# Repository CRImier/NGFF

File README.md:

# [NGFF](https://github.com/sto-pi/NGFF)

### [NGFF简介](https://github.com/sto-pi/NGFF)

[NGFF](https://github.com/sto-pi/NGFF) (Next Generation Form Factor)，与 NGFF 并列的是 2.5"（2.5”硬盘（包括HDD和SSD）厚度一般为9.5mm和7mm），NGFF现在已经改名为M.2，M.2有SATA 和PCIe两种总线标准。

M.2接口是一种新的主机接口方案，可以兼容多种通信协议，如sata、PCIe、USB、HSIC、UART、SMBus等。

M.2接口是为超极本（Ultrabook）量身定做的新一代接口标准，以取代原来的mSATA接口。无论是更小巧的规格尺寸，还是更高的传输性能，M.2都远胜于mSATA。

M.2接口，是Intel推出的一种替代MSATA新的接口规范。其实，对于桌面台式机用户来讲，SATA接口已经足以满足大部分用户的需求了，不过考虑到超极本用户的存储需求，Intel才急切的推出了这种新的接口标准。所以，我们在华硕、技嘉、微星等发布的新的9系列主板上都看到了这种新的M.2接口，现已普及。 [1]
与MSATA相比，M.2主要有两个方面的优势。第一是速度方面的优势。M.2接口有两种类型：Socket 2（B key——ngff）和Socket 3（M key——nvme），其中Socket2支持SATA、PCI-E X2接口，而如果采用PCI-E ×2接口标准，最大的读取速度可以达到700MB/s，写入也能达到550MB/s。而其中的Socket 3可支持PCI-E ×4接口，理论带宽可达4GB/s。

第二个是体积方面的优势。虽然，MSATA的固态硬盘体积已经足够小了，但相比M.2接口的固态硬盘，MSATA仍然没有任何优势可言。M.2标准的SSD同mSATA一样可以进行单面NAND闪存颗粒的布置，也可以进行双面布置，其中单面布置的总厚度仅有2.75mm，而双面布置的厚度也仅为3.85mm。而mSATA在体积上的劣势就明显的多，51mm×30mm的尺寸让mSATA在面积上不占优势，而4.85mm的单面布置厚度跟M.2比起来也显得厚了太多。另外，即使在大小相同的情况下，M.2也可以提供更高的存储容量。

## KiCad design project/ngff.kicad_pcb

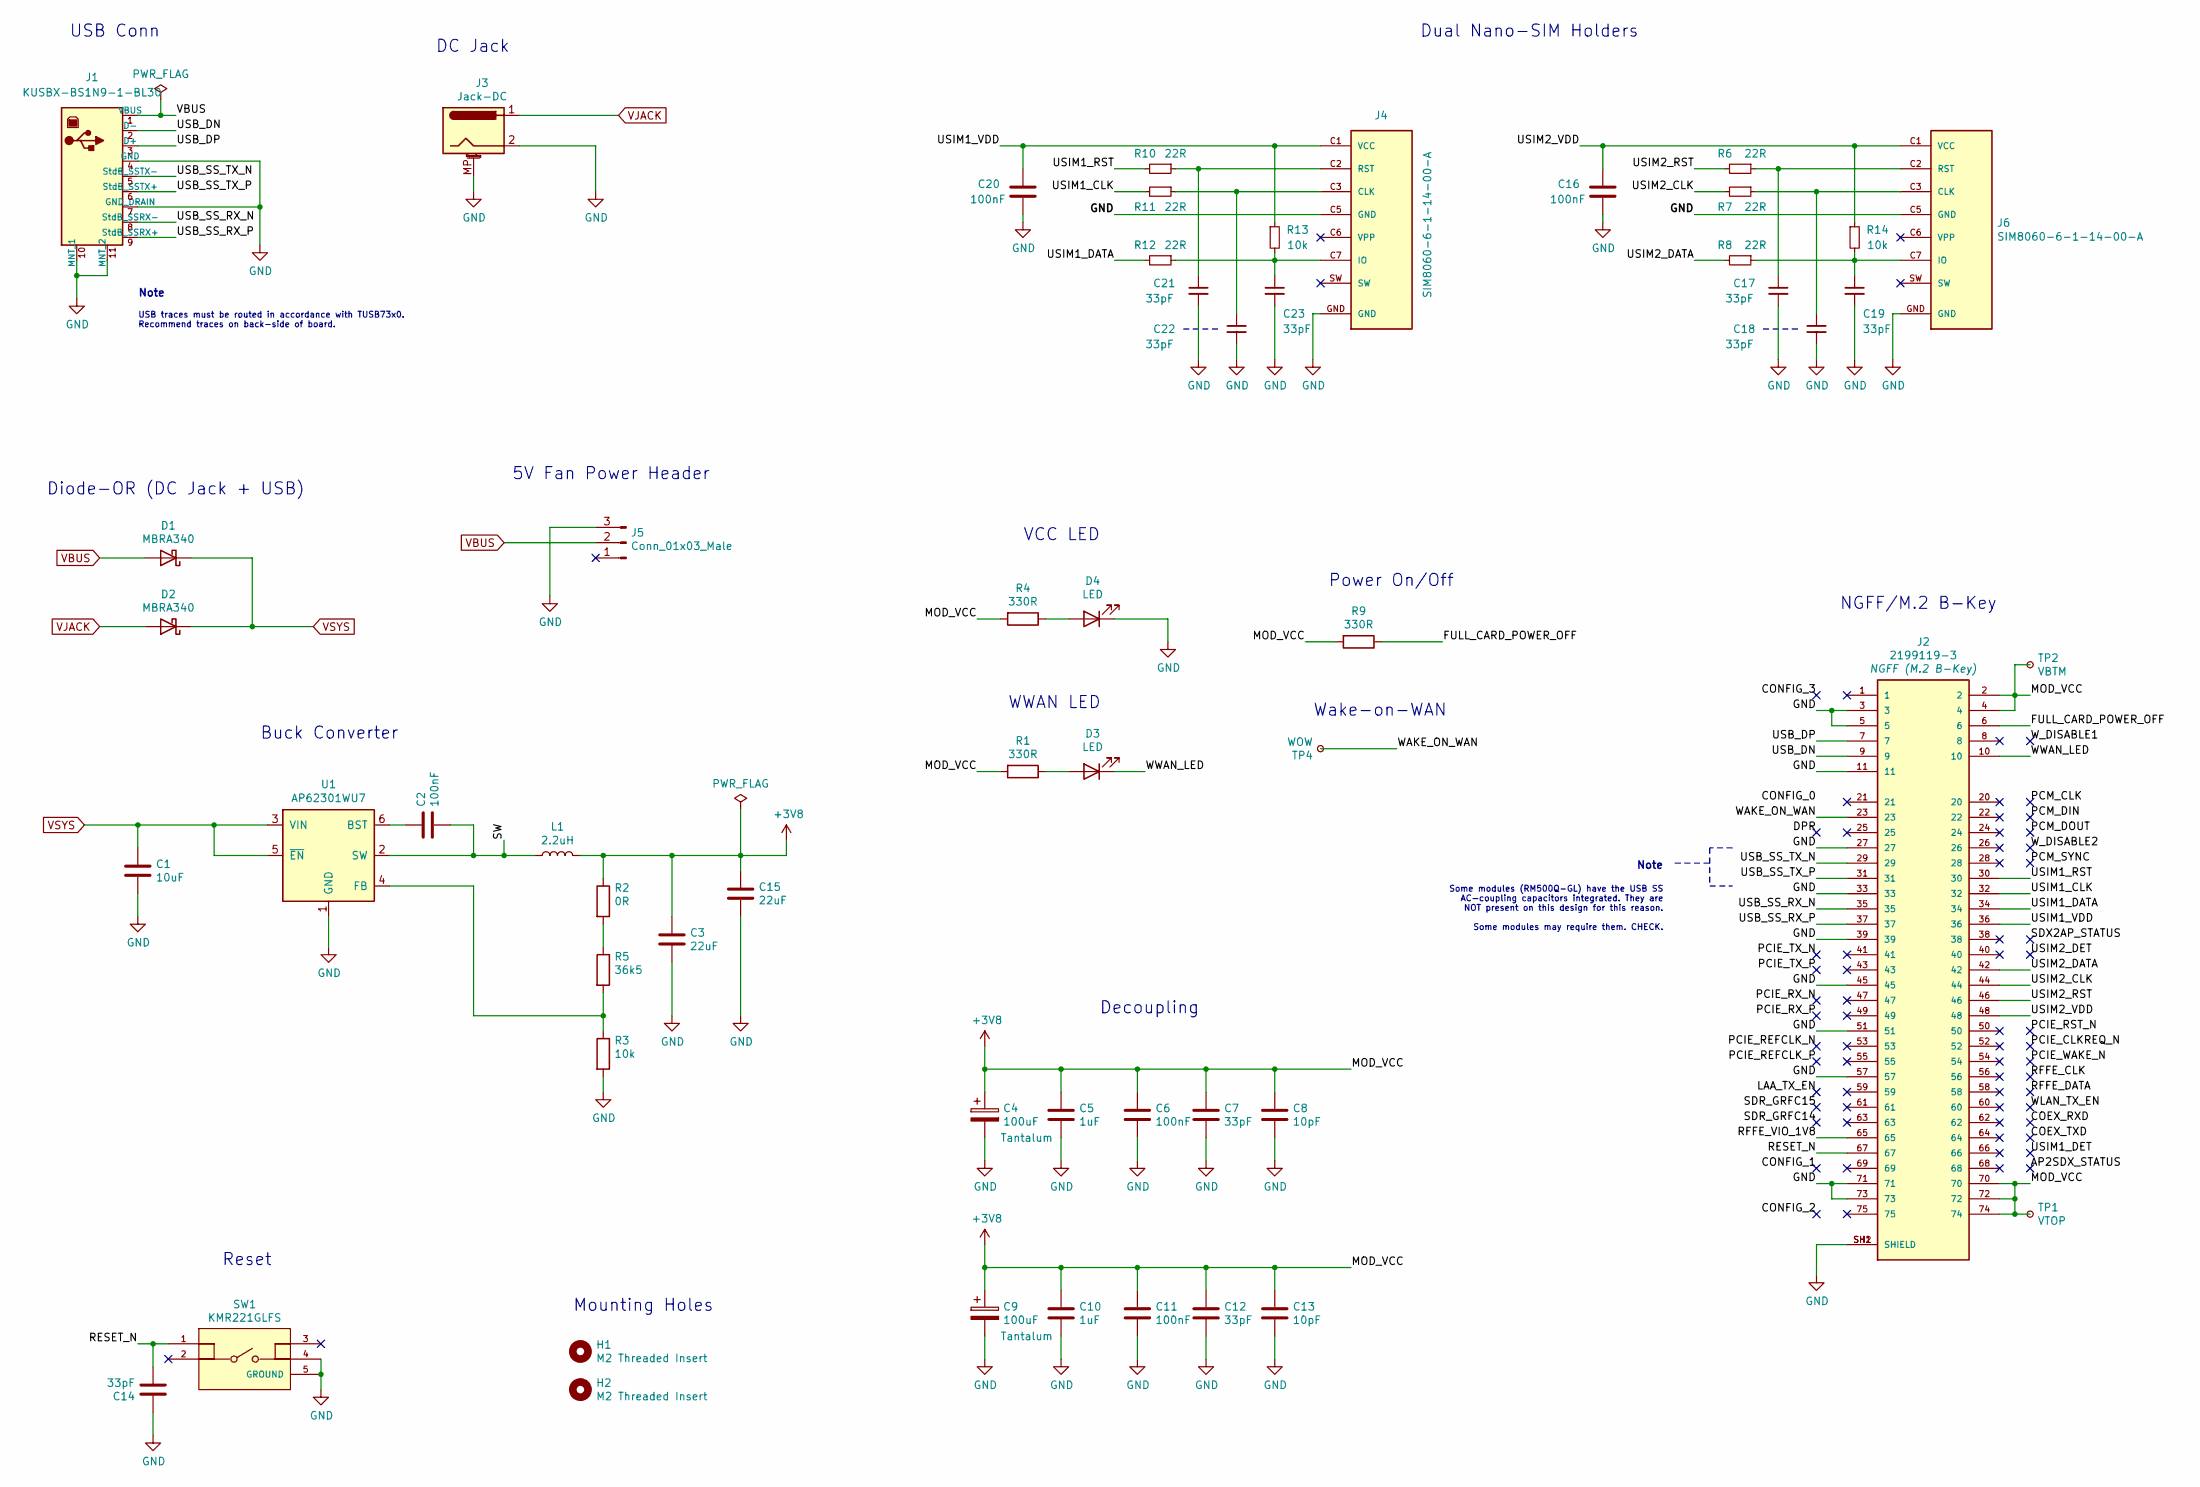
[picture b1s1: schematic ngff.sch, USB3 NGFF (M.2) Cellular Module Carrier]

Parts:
C1: 10uF; C_0805_2012Metric; MPN GRM21BR71A106KA73K
C2, C6, C11, C16, C20: 100nF; C_0603_1608Metric; MPN C0603C104K3RAC
C3, C15: 22uF; C_1210_3225Metric; MPN CL32B226MOJNNNE
C4, C9: 100uF; CP_EIA-3528-21_Kemet-B; MPN TCJB107M006R0040
C5, C10: 1uF; C_0603_1608Metric; MPN CGA3E1X7R1C105K080AC
C7, C12, C14, C17, C18, C19, C21, C22, C23: 33pF; C_0603_1608Metric; MPN 06035A330KAT2A
C8, C13: 10pF; C_0603_1608Metric; MPN 06035A100JAT4A
D1, D2: MBRA340; D_SMA; MPN MBRA340T3G
D3, D4: LED; LED_0805_2012Metric; MPN APTD2012LQBC/D
H1, H2: M2 Threaded Insert; 9774015243RStandoff; MPN 9774015243R
J1: KUSBX-BS1N9-1-BL30; Wurth-692221030100-0-0-MFG; MPN KUSBX-BS1N9-1-BL30
J2: 2199119-3; TE_2199119-3; MPN 2199119-3
J3: Jack-DC; BarrelJack_Wuerth_6941xx301002; MPN 694106301002
J4, J6: SIM8060-6-1-14-00-A; GCT_SIM8060-6-1-14-00-A; MPN SIM8060-6-1-14-00-A
J5: Conn_01x03_Male; PinHeader_1x03_P2.54mm_Vertical
L1: 2.2uH; L_Coilcraft_XAL5030; MPN XAL5030-222MEC
R1, R4, R9: 330R; R_0603_1608Metric
R2: 0R; R_0603_1608Metric
R3, R13, R14: 10k; R_0603_1608Metric
R5: 36k5; R_0603_1608Metric; MPN CRCW060336K5FKEA
R6, R7, R8, R10, R11, R12: 22R; R_0603_1608Metric
SW1: KMR221GLFS; CK-KMR221GLFS-MFG; MPN KMR221GLFS
TP1: VTOP; TestPoint_Pad_D1.5mm
TP2: VBTM; TestPoint_Pad_D1.5mm
TP4: WOW; TestPoint_Pad_D1.5mm
U1: AP62301WU7; TSOT-23-6; MPN AP62301WU-7

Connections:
+3V8: C3.1, C4.1, C5.1, C6.1, C7.1, C8.1, C9.1, C10.1, C11.1, C12.1, C13.1, C15.1, J2.2, J2.4, J2.70, J2.72, J2.74, L1.2, R1.2, R2.1, R4.2, R9.2, TP1.1, TP2.1
/FULL_CARD_POWER_OFF: J2.6, R9.1
/RESET_N: C14.2, J2.67, SW1.1
/RFFE_VIO_1V8: J2.65
/SW: C2.2, L1.1, U1.2 (SW)
/USB_DN: J1.2 (D-), J2.9
/USB_DP: J1.3 (D+), J2.7
/USB_SS_RX_N: J1.8 (StdB_SSRX-), J2.35
/USB_SS_RX_P: J1.9 (StdB_SSRX+), J2.37
/USB_SS_TX_N: J1.5 (StdB_SSTX-), J2.29
/USB_SS_TX_P: J1.6 (StdB_SSTX+), J2.31
/USIM1_CLK: J2.32, R11.2
/USIM1_DATA: J2.34, R12.2
/USIM1_RST: J2.30, R10.2
/USIM1_VDD: C20.1, J2.36, J4.C1 (VCC), R13.1
/USIM2_CLK: J2.44, R7.2
/USIM2_DATA: J2.42, R8.2
/USIM2_RST: J2.46, R6.2
/USIM2_VDD: C16.1, J2.48, J6.C1 (VCC), R14.1
/WAKE_ON_WAN: J2.23, TP4.1
/WWAN_LED: D3.1 (K), J2.10
GND: C1.2, C3.2, C4.2, C5.2, C6.2, C7.2, C8.2, C9.2, C10.2, C11.2, C12.2, C13.2, C14.1, C15.2, C16.2, C17.2, C18.2, C19.2, C20.2, C21.2, C22.2, C23.2, D4.1 (K), J1.4 (GND), J1.7 (GND_DRAIN), J1.10 (MNT_1), J1.11 (MNT_2), J2.3, J2.5, J2.11, J2.27, J2.33, J2.39, J2.45, J2.51, J2.57, J2.71, J2.73, J2.SH1 (SHIELD), J2.SH2 (SHIELD), J3.2, J3.MP (MountPin), J4.C5 (GND), J4.GND, J5.3, J6.C5 (GND), J6.GND, R3.2, SW1.4, SW1.5 (GROUND), U1.1 (GND)
unnamed: C2.1, U1.6 (BST)
unnamed: C17.1, J6.C2 (RST), R6.1
unnamed: C18.1, J6.C3 (CLK), R7.1
unnamed: C19.1, J6.C7 (IO), R8.1, R14.2
unnamed: C21.1, J4.C2 (RST), R10.1
unnamed: C22.1, J4.C3 (CLK), R11.1
unnamed: C23.1, J4.C7 (IO), R12.1, R13.2
unnamed: D3.2 (A), R1.1
unnamed: D4.2 (A), R4.1
unnamed: R2.2, R5.1
unnamed: R3.1, R5.2, U1.4 (FB)
VBUS: D1.2 (A), J1.1 (VBUS), J5.2
VJACK: D2.2 (A), J3.1
VSYS: C1.1, D1.1 (K), D2.1 (K), U1.3 (VIN), U1.5 (~EN)

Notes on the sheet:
Dual Nano-SIM Holders
VCC LED
WWAN LED
Reset
5V Fan Power Header
Diode-OR (DC Jack + USB)
USB Conn
DC Jack
Power On/Off
Decoupling
NGFF/M.2 B-Key
Wake-on-WAN
Mounting Holes
Note
Some modules (RM500Q-GL) have the USB SS AC-coupling capacitors integrated. They are NOT present on this design for this reason. Some modules may require them. CHECK.
USB traces must be routed in accordance with TUSB73x0. Recommend traces on back-side of board.
Buck Converter

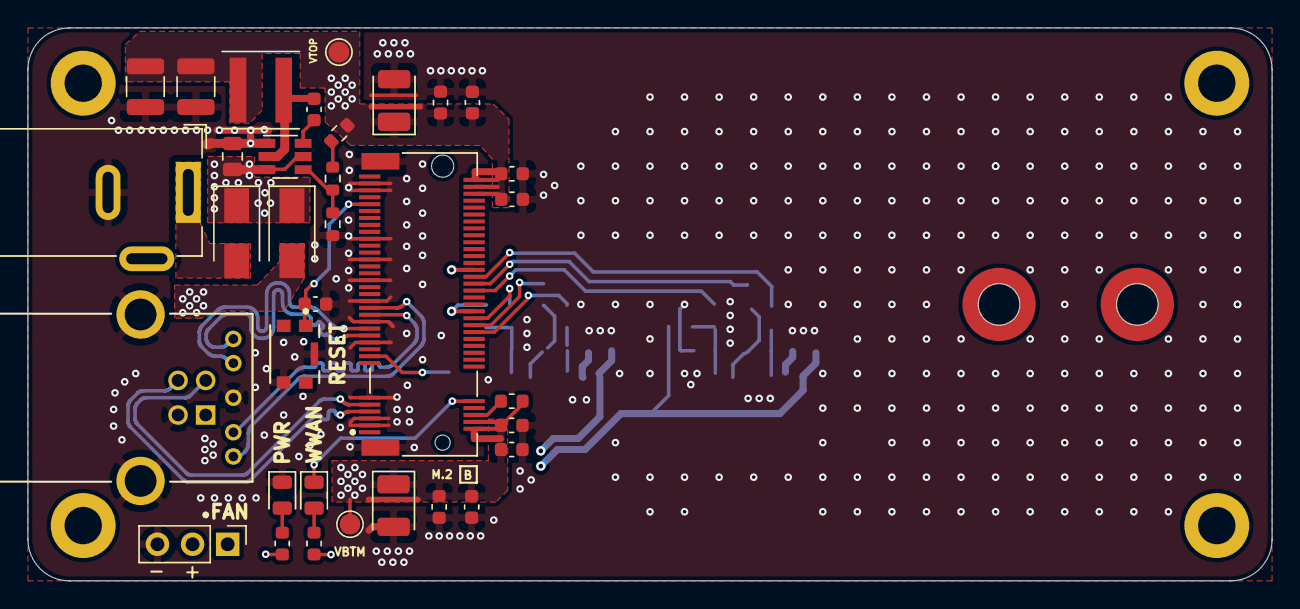
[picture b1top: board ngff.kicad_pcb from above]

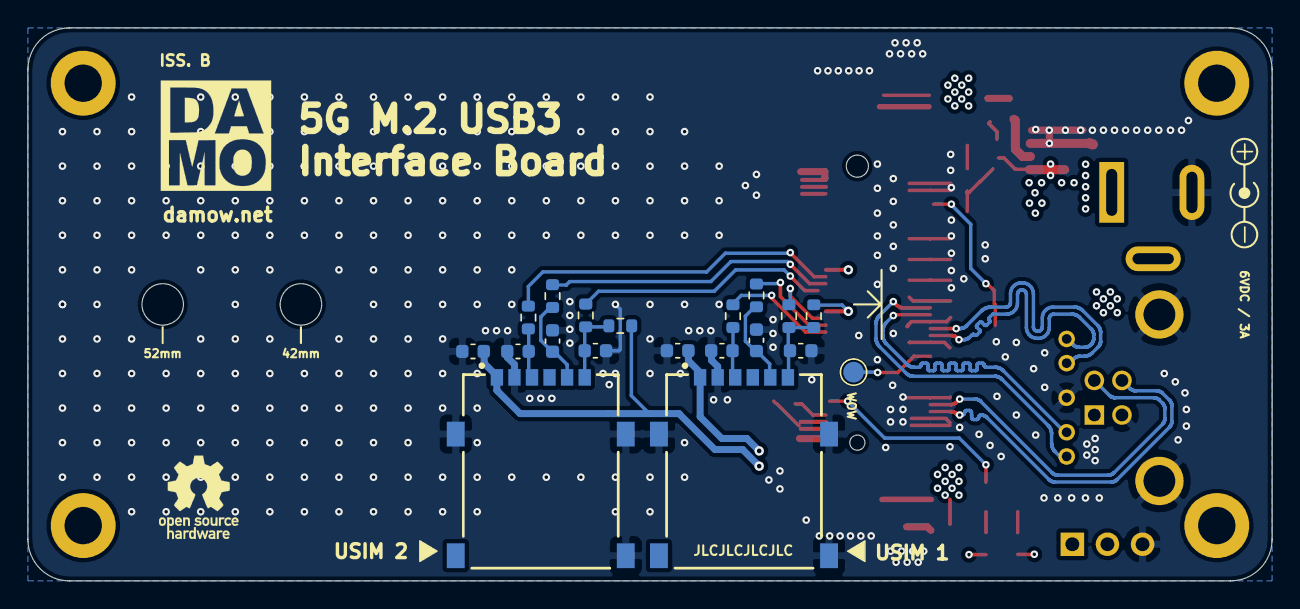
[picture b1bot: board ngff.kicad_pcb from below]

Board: 4 copper layers, 90.0 x 40.0 mm, 55 parts (19 on the bottom side), 35 nets.

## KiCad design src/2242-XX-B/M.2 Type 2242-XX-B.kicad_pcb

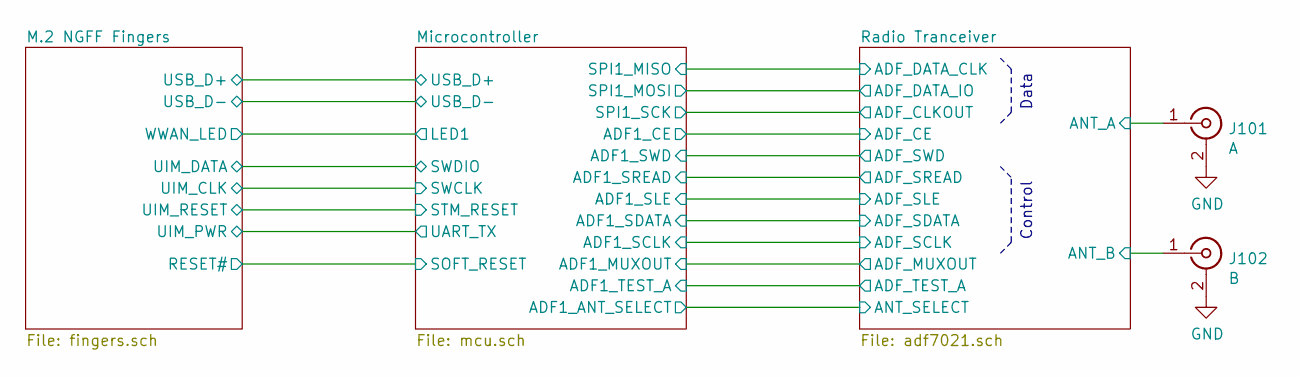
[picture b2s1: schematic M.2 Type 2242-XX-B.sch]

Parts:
J101: A; U.FL_Hirose_U.FL-R-SMT-1_Vertical
J102: B; U.FL_Hirose_U.FL-R-SMT-1_Vertical

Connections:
/Radio Tranceiver/ANT_A: J101.1 (In); also elsewhere on the board
/Radio Tranceiver/ANT_B: J102.1 (In); also elsewhere on the board
GND: J101.2 (Ext), J102.2 (Ext); also elsewhere on the board

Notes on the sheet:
Control
Data

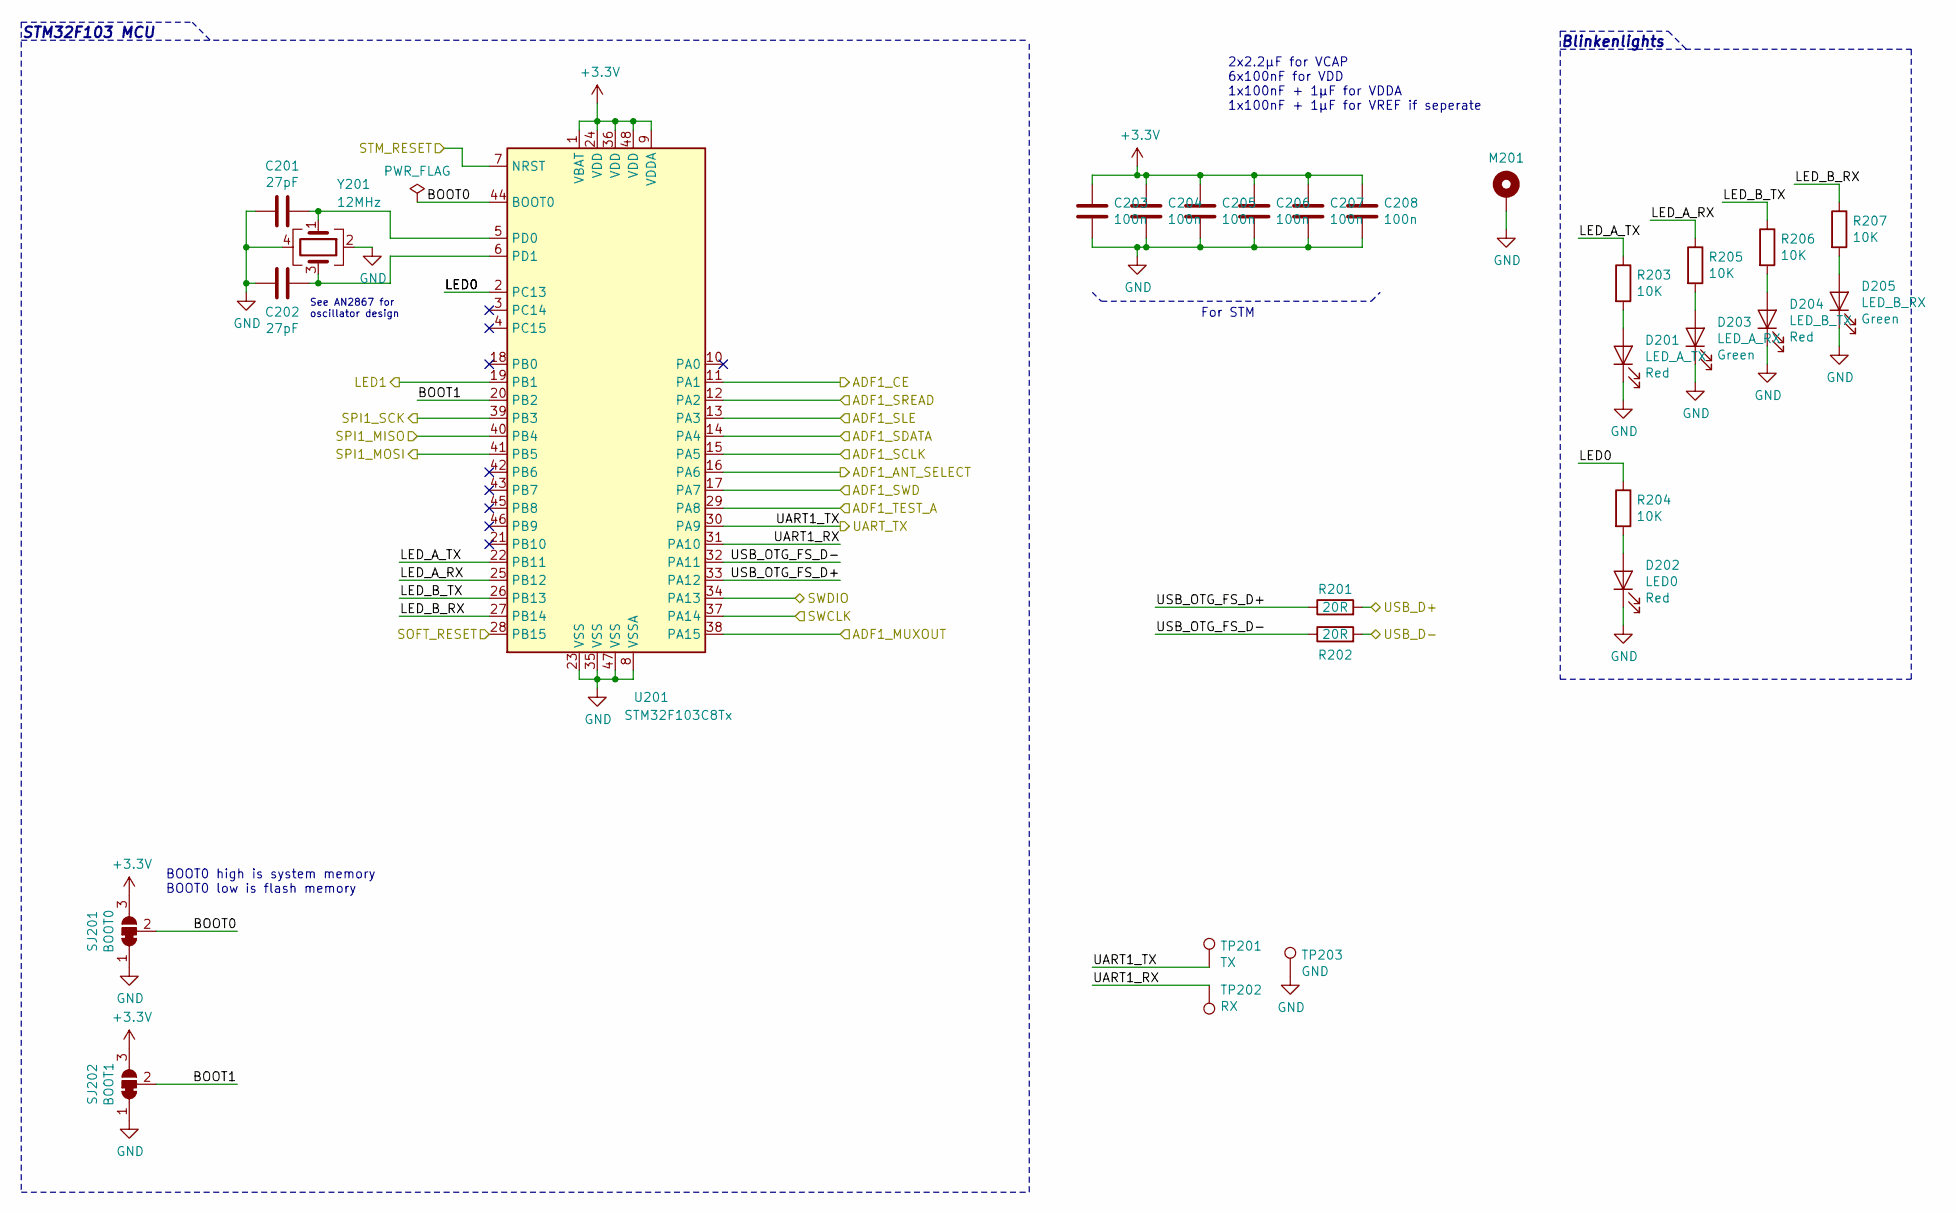
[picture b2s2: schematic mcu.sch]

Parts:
C201, C202: 27pF; C_0603_1608Metric
C203, C204, C205, C206, C207, C208: 100n; C_0603_1608Metric
D201: LED_A_TX; LED_0603_1608Metric
D202: LED0; LED_0603_1608Metric
D203: LED_A_RX; LED_0603_1608Metric
D204: LED_B_TX; LED_0603_1608Metric
D205: LED_B_RX; LED_0603_1608Metric
M201: MountingHole_Pad; M.2_Standoff_Card_Pad
R201, R202: 20R; R_0603_1608Metric
R203, R204, R205, R206, R207: 10K; R_0603_1608Metric
SJ201: BOOT0; SolderJumper-3_P1.3mm_Bridged12_RoundedPad1.0x1.5mm
SJ202: BOOT1; SolderJumper-3_P1.3mm_Bridged12_RoundedPad1.0x1.5mm
TP201: TX; TestPad
TP202: RX; TestPad
TP203: GND; TestPad
U201: STM32F103C8Tx; LQFP-48_7x7mm_P0.5mm
Y201: 12MHz; Crystal_SMD_3225-4Pin_3.2x2.5mm; digikey# 1923-1568-1-ND

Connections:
+3V3: C203.1, C204.1, C205.1, C206.1, C207.1, C208.1, SJ201.3 (B), SJ202.3 (B), U201.1 (VBAT), U201.9 (VDDA), U201.24 (VDD), U201.36 (VDD), U201.48 (VDD); also elsewhere on the board
/M.2 NGFF Fingers/RESET#: U201.28 (PB15); also elsewhere on the board
/M.2 NGFF Fingers/USB_D+: R201.2; also elsewhere on the board
/M.2 NGFF Fingers/USB_D-: R202.2; also elsewhere on the board
/Microcontroller/ADF1_ANT_SELECT: U201.16 (PA6); also elsewhere on the board
/Microcontroller/ADF1_CE: U201.11 (PA1); also elsewhere on the board
/Microcontroller/ADF1_MUXOUT: U201.38 (PA15); also elsewhere on the board
/Microcontroller/ADF1_SCLK: U201.15 (PA5); also elsewhere on the board
/Microcontroller/ADF1_SDATA: U201.14 (PA4); also elsewhere on the board
/Microcontroller/ADF1_SLE: U201.13 (PA3); also elsewhere on the board
/Microcontroller/ADF1_SREAD: U201.12 (PA2); also elsewhere on the board
/Microcontroller/ADF1_SWD: U201.17 (PA7); also elsewhere on the board
/Microcontroller/ADF1_TEST_A: U201.29 (PA8); also elsewhere on the board
/Microcontroller/BOOT0: SJ201.2 (C), U201.44 (BOOT0)
/Microcontroller/BOOT1: SJ202.2 (C), U201.20 (PB2)
/Microcontroller/LED0: R204.1, U201.2 (PC13)
/Microcontroller/LED1: U201.19 (PB1); also elsewhere on the board
/Microcontroller/LED_A_RX: R205.1, U201.25 (PB12)
/Microcontroller/LED_A_TX: R203.1, U201.22 (PB11)
/Microcontroller/LED_B_RX: R207.1, U201.27 (PB14)
/Microcontroller/LED_B_TX: R206.1, U201.26 (PB13)
/Microcontroller/STM_RESET: U201.7 (NRST); also elsewhere on the board
/Microcontroller/SWCLK: U201.37 (PA14); also elsewhere on the board
/Microcontroller/SWDIO: U201.34 (PA13); also elsewhere on the board
/Microcontroller/UART1_RX: TP202.1, U201.31 (PA10)
/Microcontroller/UART_TX: TP201.1, U201.30 (PA9); also elsewhere on the board
/Microcontroller/USB_OTG_FS_D+: R201.1, U201.33 (PA12)
/Microcontroller/USB_OTG_FS_D-: R202.1, U201.32 (PA11)
/Radio Tranceiver/ADF_CLKOUT: U201.39 (PB3); also elsewhere on the board
/Radio Tranceiver/ADF_DATA_CLK: U201.40 (PB4); also elsewhere on the board
/Radio Tranceiver/ADF_DATA_IO: U201.41 (PB5); also elsewhere on the board
GND: C201.2, C202.2, C203.2, C204.2, C205.2, C206.2, C207.2, C208.2, D201.1 (K), D202.1 (K), D203.1 (K), D204.1 (K), D205.1 (K), M201.1, SJ201.1 (A), SJ202.1 (A), TP203.1, U201.8 (VSSA), U201.23 (VSS), U201.35 (VSS), U201.47 (VSS), Y201.2, Y201.4; also elsewhere on the board
unnamed: C201.1, U201.5 (PD0), Y201.1
unnamed: C202.1, U201.6 (PD1), Y201.3
unnamed: D201.2 (A), R203.2
unnamed: D202.2 (A), R204.2
unnamed: D203.2 (A), R205.2
unnamed: D204.2 (A), R206.2
unnamed: D205.2 (A), R207.2

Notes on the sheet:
See AN2867 for oscillator design
STM32F103 MCU
Blinkenlights
2x2.2µF for VCAP 6x100nF for VDD 1x100nF + 1µF for VDDA 1x100nF + 1µF for VREF if seperate
For STM
BOOT0 high is system memory BOOT0 low is flash memory

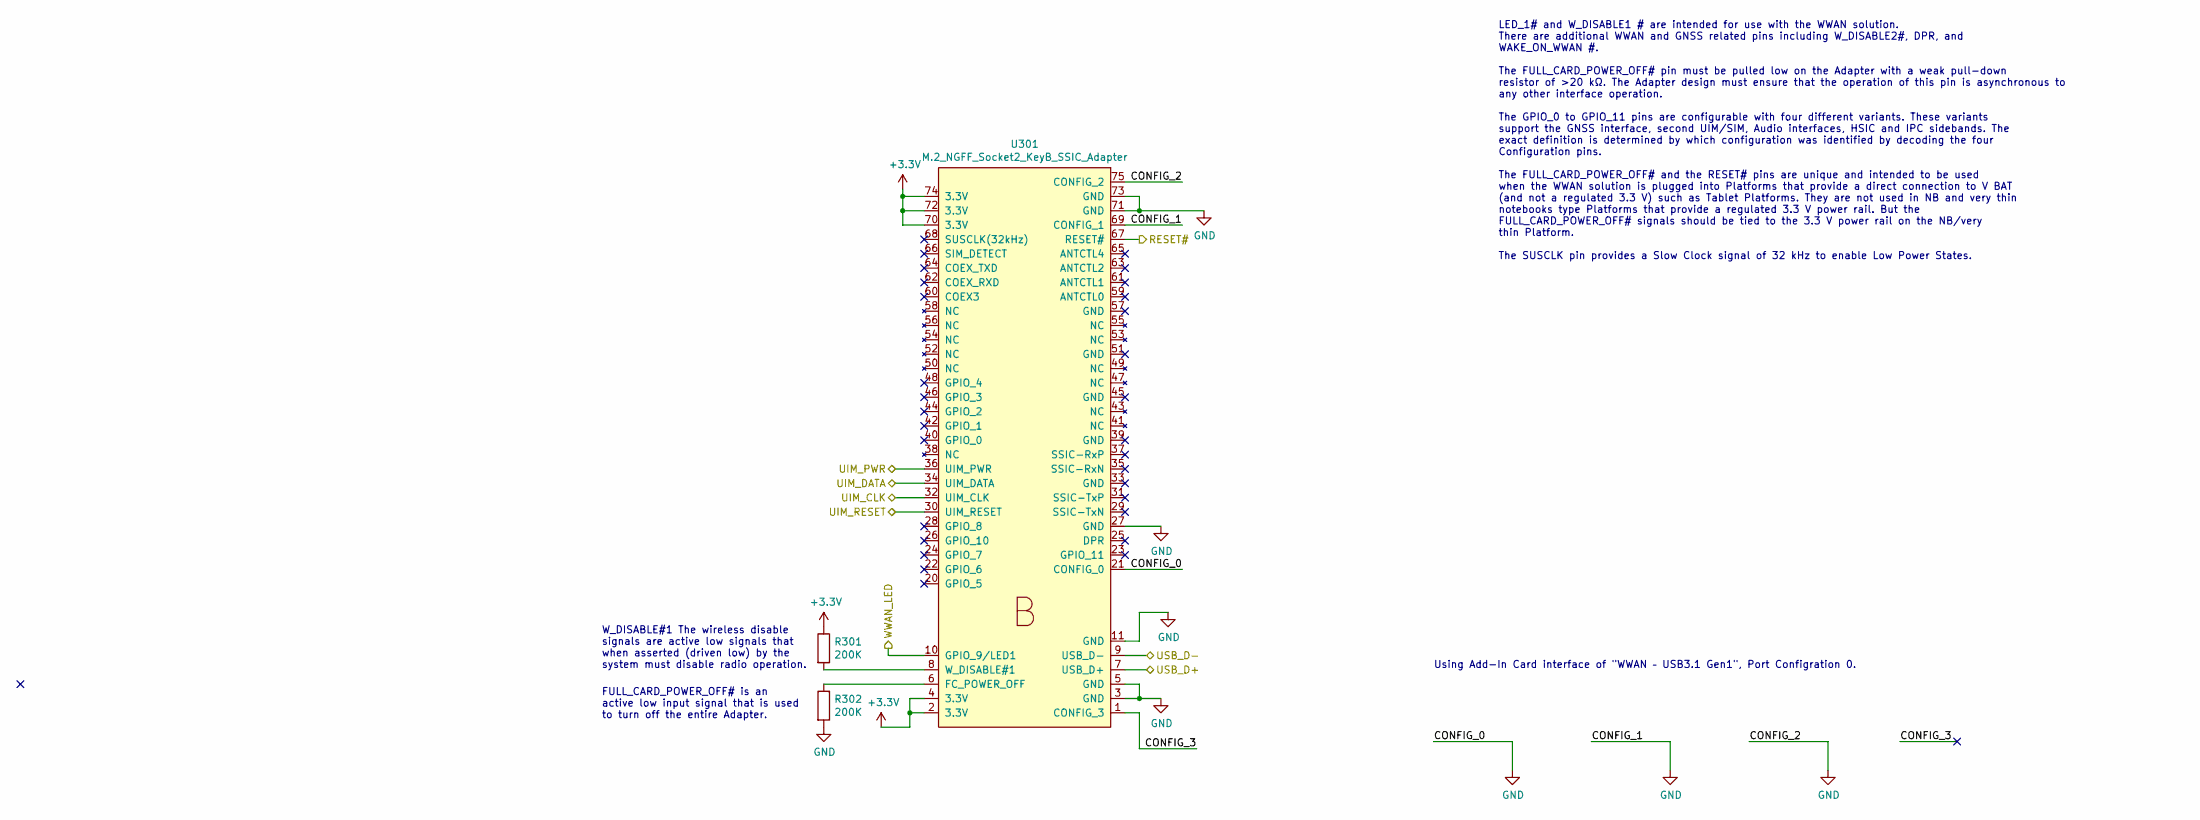
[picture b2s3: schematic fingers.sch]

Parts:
R301, R302: 200K; R_0603_1608Metric
U301: M.2_NGFF_Socket2_KeyB_SSIC_Adapter; M.2_Key_B_Fingers

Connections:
+3V3: R301.1, U301.2 (3.3V), U301.4 (3.3V), U301.70 (3.3V), U301.72 (3.3V), U301.74 (3.3V); also elsewhere on the board
/M.2 NGFF Fingers/CONFIG_3: U301.1 (CONFIG_3)
/M.2 NGFF Fingers/RESET#: U301.67 (RESET#); also elsewhere on the board
/M.2 NGFF Fingers/USB_D+: U301.7 (USB_D+); also elsewhere on the board
/M.2 NGFF Fingers/USB_D-: U301.9 (USB_D-); also elsewhere on the board
/Microcontroller/LED1: U301.10 (GPIO_9/LED1); also elsewhere on the board
/Microcontroller/STM_RESET: U301.30 (UIM_RESET); also elsewhere on the board
/Microcontroller/SWCLK: U301.32 (UIM_CLK); also elsewhere on the board
/Microcontroller/SWDIO: U301.34 (UIM_DATA); also elsewhere on the board
/Microcontroller/UART_TX: U301.36 (UIM_PWR); also elsewhere on the board
GND: R302.2, U301.3 (GND), U301.5 (GND), U301.11 (GND), U301.21 (CONFIG_0), U301.27 (GND), U301.69 (CONFIG_1), U301.71 (GND), U301.73 (GND), U301.75 (CONFIG_2); also elsewhere on the board
unnamed: R301.2, U301.8 (W_DISABLE#1)
unnamed: R302.1, U301.6 (FC_POWER_OFF)

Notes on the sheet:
LED_1# and W_DISABLE1 # are intended for use with the WWAN solution. There are additional WWAN and GNSS related pins including W_DISABLE2#, DPR, and WAKE_ON_WWAN #. The FULL_CARD_POWER_OFF# pin must be pulled low on the Adapter with a weak pull-down resistor of >20 kΩ. The Adapter design must ensur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
FULL_CARD_POWER_OFF# is an active low input signal that is used to turn off the entire Adapter.
W_DISABLE#1 The wireless disable signals are active low signals that when asserted (driven low) by the system must disable radio operation.
Using Add-In Card interface of "WWAN – USB3.1 Gen1", Port Configration 0.

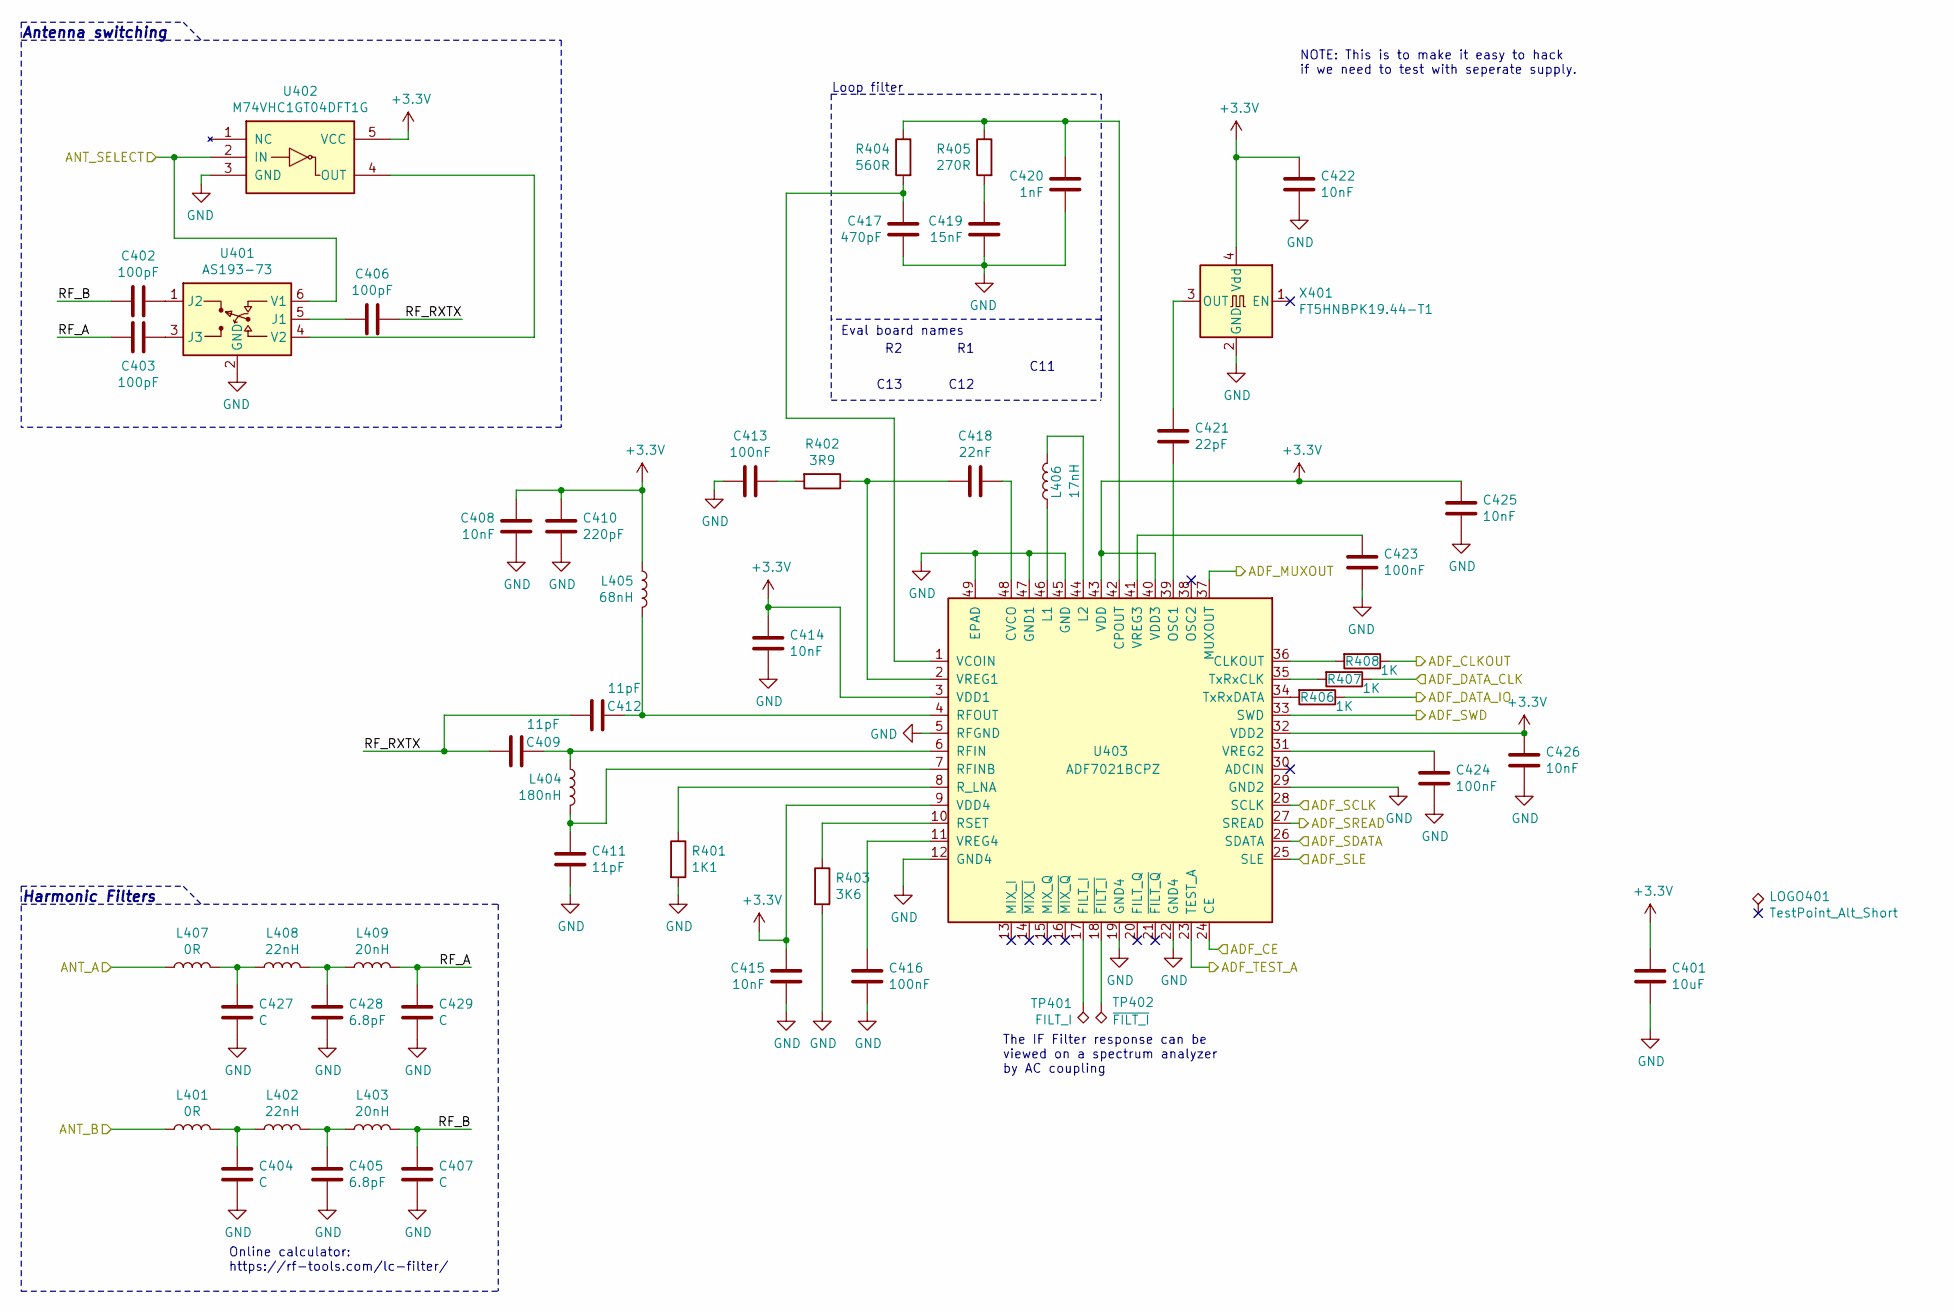
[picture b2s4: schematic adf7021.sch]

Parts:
C401: 10uF; C_0805_2012Metric
C402, C403, C406: 100pF; C_0603_1608Metric
C404, C407, C427, C429: C; C_0603_1608Metric
C405, C428: 6.8pF; C_0603_1608Metric
C408, C414, C415, C422, C425, C426: 10nF; C_0603_1608Metric
C409, C411, C412: 11pF; C_0603_1608Metric
C410: 220pF; C_0603_1608Metric
C413, C416, C423, C424: 100nF; C_0603_1608Metric
C417: 470pF; C_0603_1608Metric
C418: 22nF; C_0603_1608Metric
C419: 15nF; C_0603_1608Metric
C420: 1nF; C_0603_1608Metric
C421: 22pF; C_0603_1608Metric
L401, L407: 0R; L_0603_1608Metric
L402, L408: 22nH; L_0603_1608Metric
L403, L409: 20nH; L_0603_1608Metric
L404: 180nH; L_0603_1608Metric
L405: 68nH; L_0603_1608Metric
L406: 17nH; L_0603_1608Metric
LOGO401: TestPoint_Alt_Short; KiCad-Logo_Back
R401: 1K1; R_0603_1608Metric
R402: 3R9; R_0603_1608Metric
R403: 3K6; R_0603_1608Metric
R404: 560R; R_0603_1608Metric
R405: 270R; R_0603_1608Metric
R406, R407, R408: 1K; R_0603_1608Metric
TP401: FILT_I; TestPad
TP402: ~FILT_I; TestPad
U401: AS193-73; SuperSOT-6
U402: M74VHC1GT04DFT1G; SOT-353_SC-70-5; digikey# M74VHC1GT04DFT1GOSCT-ND
U403: ADF7021BCPZ; LFCSP-48-1EP_7x7mm_P0.5mm_EP4.1x4.1mm_ThermalVias
X401: FT5HNBPK19.44-T1; FOX924; digikey# 631-1072-1-ND

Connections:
+3V3: C401.1, C408.1, C410.1, C414.1, C415.1, C422.1, C425.1, C426.1, L405.1, U402.5 (VCC), U403.3 (VDD1), U403.9 (VDD4), U403.32 (VDD2), U403.40 (VDD3), U403.43 (VDD), X401.4 (Vdd); also elsewhere on the board
/Microcontroller/ADF1_ANT_SELECT: U401.6 (V1), U402.2 (IN); also elsewhere on the board
/Microcontroller/ADF1_CE: U403.24 (CE); also elsewhere on the board
/Microcontroller/ADF1_MUXOUT: U403.37 (MUXOUT); also elsewhere on the board
/Microcontroller/ADF1_SCLK: U403.28 (SCLK); also elsewhere on the board
/Microcontroller/ADF1_SDATA: U403.26 (SDATA); also elsewhere on the board
/Microcontroller/ADF1_SLE: U403.25 (SLE); also elsewhere on the board
/Microcontroller/ADF1_SREAD: U403.27 (SREAD); also elsewhere on the board
/Microcontroller/ADF1_SWD: U403.33 (SWD); also elsewhere on the board
/Microcontroller/ADF1_TEST_A: U403.23 (TEST_A); also elsewhere on the board
/Radio Tranceiver/ADF_CLKOUT: R408.1; also elsewhere on the board
/Radio Tranceiver/ADF_DATA_CLK: R407.1; also elsewhere on the board
/Radio Tranceiver/ADF_DATA_IO: R406.1; also elsewhere on the board
/Radio Tranceiver/ANT_A: L407.1; also elsewhere on the board
/Radio Tranceiver/ANT_B: L401.1; also elsewhere on the board
/Radio Tranceiver/RF_A: C403.2, C429.1, L409.2
/Radio Tranceiver/RF_B: C402.2, C407.1, L403.2
/Radio Tranceiver/RF_RXTX: C406.1, C409.1, C412.1
GND: C401.2, C404.2, C405.2, C407.2, C408.2, C410.2, C411.2, C413.2, C414.2, C415.2, C416.2, C417.2, C419.2, C420.2, C422.2, C423.2, C424.2, C425.2, C426.2, C427.2, C428.2, C429.2, R401.2, R403.2, U401.2 (GND), U402.3 (GND), U403.5 (RFGND), U403.12 (GND4), U403.19 (GND4), U403.22 (GND4), U403.29 (GND2), U403.45 (GND), U403.47 (GND1), U403.49 (EPAD), X401.2 (GND); also elsewhere on the board
unnamed: C402.1, U401.1 (J2)
unnamed: C403.1, U401.3 (J3)
unnamed: C404.1, L401.2, L402.1
unnamed: C405.1, L402.2, L403.1
unnamed: C406.2, U401.5 (J1)
unnamed: C409.2, L404.1, U403.6 (RFIN)
unnamed: C411.1, L404.2, U403.7 (RFINB)
unnamed: C412.2, L405.2, U403.4 (RFOUT)
unnamed: C413.1, R402.2
unnamed: C416.1, U403.11 (VREG4)
unnamed: C417.1, R404.2, U403.1 (VCOIN)
unnamed: C418.1, U403.48 (CVCO)
unnamed: C418.2, R402.1, U403.2 (VREG1)
unnamed: C419.1, R405.2
unnamed: C420.1, R404.1, R405.1, U403.42 (CPOUT)
unnamed: C421.1, X401.3 (OUT)
unnamed: C421.2, U403.39 (OSC1)
unnamed: C423.1, U403.41 (VREG3)
unnamed: C424.1, U403.31 (VREG2)
unnamed: C427.1, L407.2, L408.1
unnamed: C428.1, L408.2, L409.1
unnamed: L406.1, U403.46 (L1)
unnamed: L406.2, U403.44 (L2)
unnamed: R401.1, U403.8 (R_LNA)
unnamed: R403.1, U403.10 (RSET)
unnamed: R406.2, U403.34 (TxRxDATA)
unnamed: R407.2, U403.35 (TxRxCLK)
unnamed: R408.2, U403.36 (CLKOUT)
unnamed: TP401.1, U403.17 (FILT_I)
unnamed: TP402.1, U403.18 (~FILT_I)
unnamed: U401.4 (V2), U402.4 (OUT)

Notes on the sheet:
Antenna switching
NOTE: This is to make it easy to hack if we need to test with seperate supply.
The IF Filter response can be viewed on a spectrum analyzer by AC coupling
Loop filter
Eval board names
C13
C12
C11
Online calculator: https://rf-tools.com/lc-filter/
Harmonic Filters

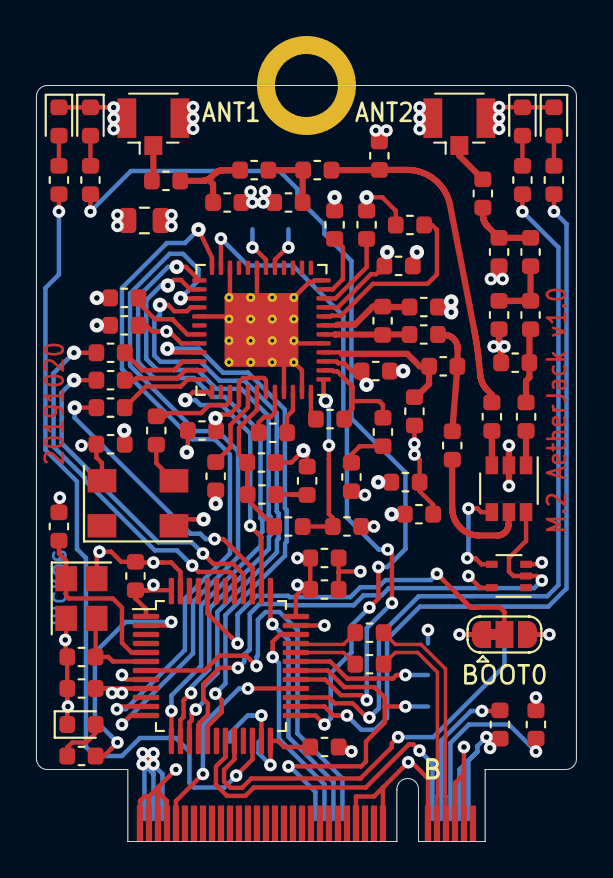
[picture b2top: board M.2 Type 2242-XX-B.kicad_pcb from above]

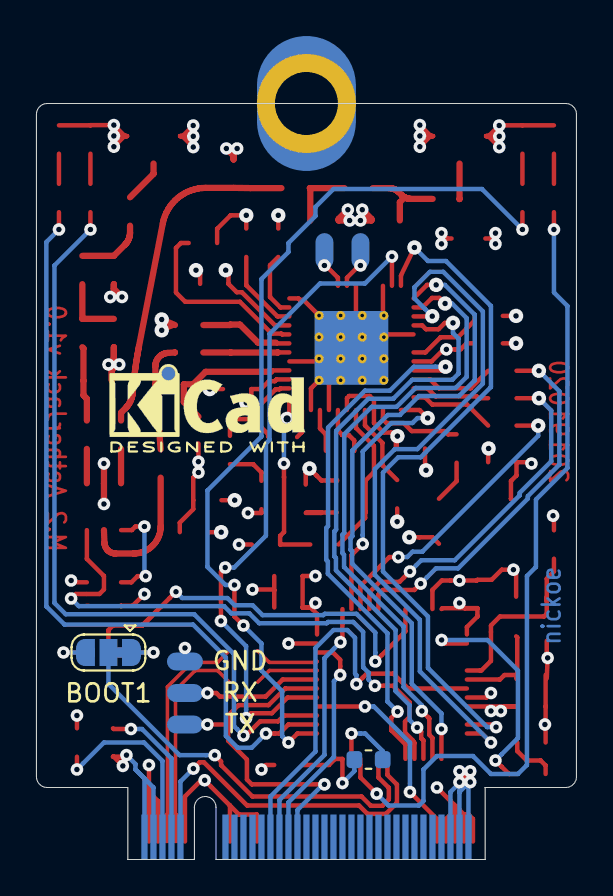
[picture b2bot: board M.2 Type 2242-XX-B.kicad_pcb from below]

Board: 4 copper layers, 30.0 x 42.0 mm, 86 parts (8 on the bottom side), 77 nets.

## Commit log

2019-05-27 init
2020-03-03 fix folder
2020-03-03 fix add
2020-03-03 add project
2020-03-03 add mcu templetes
2021-10-21 United keying information; added G key; able to do A+E keying now
    I removed unused keying dictionary parameters - R,S,T,U,W,X,Y,Z.
    I then united keyingSecond and keyingFirst into one dictionaries,
    inverted V calculation for secondKey and then inverted V (KeyCenter) parameter
    so that key offset parameters would be the same direction for all keys.
    Generating A+E card with "E" as first and "A" as second results in garbage.
    I also added sanity check logic that checks the key alphabetic order
2021-10-21 Fixed the A+E footprint generation by refactoring bottom horizontal line drawing out of first_key+second_key block into the bottom endpoint processing block, together with soldermask opening calculat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
2021-10-21 Fixed a bug where my order checking code would fail on single-notch cards
2021-10-21 Refactored the key (notch) generation code, now less verbose and easier to modify if needed.
2021-10-21 Shortened even further - now could add 3+ key support if you *really* wanted =D
